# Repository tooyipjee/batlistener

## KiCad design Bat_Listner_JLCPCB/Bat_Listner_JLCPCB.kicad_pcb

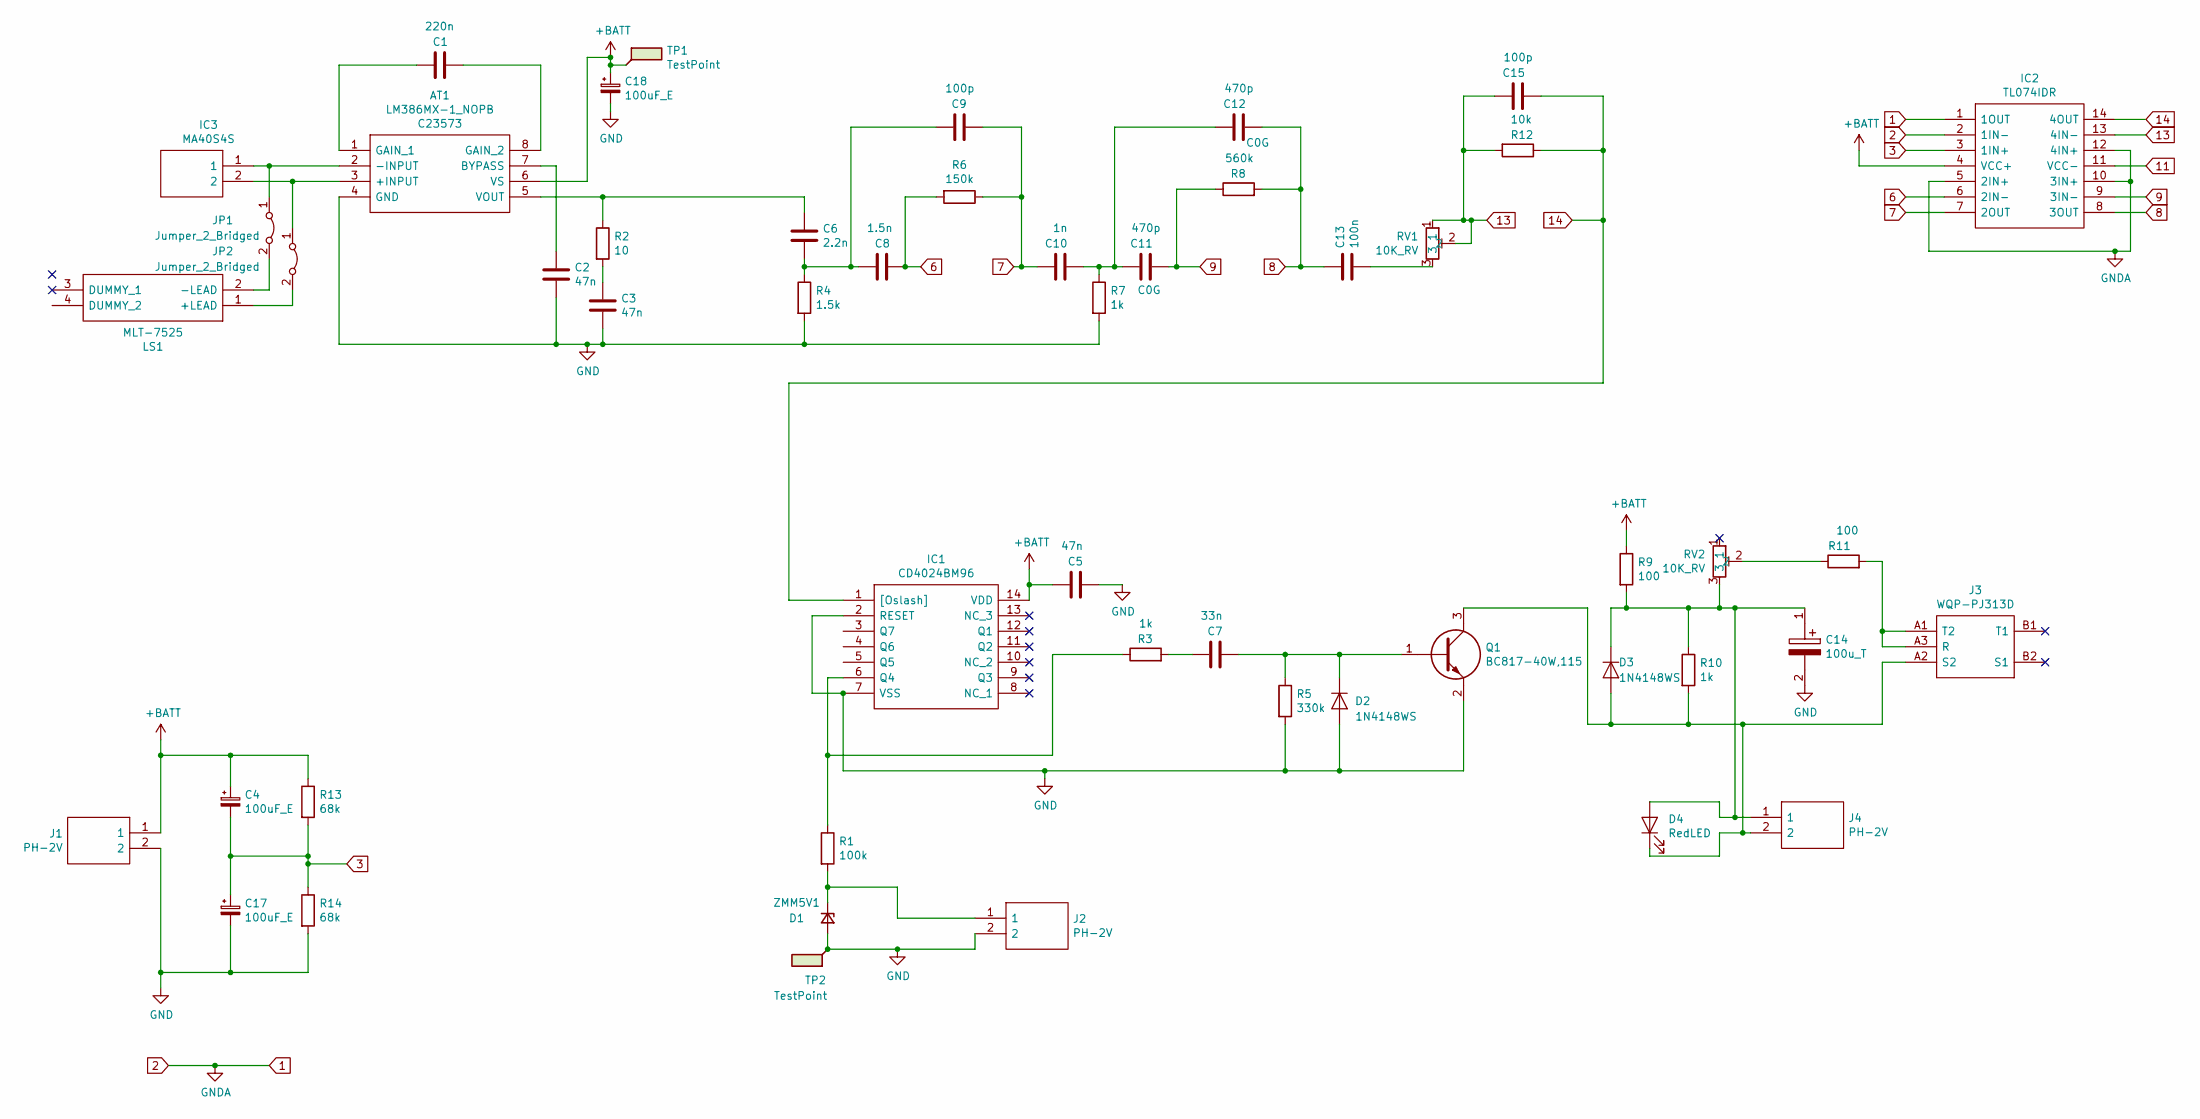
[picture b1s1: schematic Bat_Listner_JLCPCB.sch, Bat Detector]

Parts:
AT1: LM386MX-1_NOPB; SOIC127P600X175-8N; Manufacturer_Part_Number LM386MX-1/NOPB; Mouser Part Number 926-LM386MX-1/NOPB
C1: 220n; C_0402_1005Metric; LCSC C16772
C2, C3, C5: 47n; C_0402_1005Metric; LCSC C26403
C4, C17, C18: 100uF_E; CP_Elec_6.3x7.7; Rating 25V; LCSC C127971
C6: 2.2n; C_0402_1005Metric; LCSC C1531
C7: 33n; C_0402_1005Metric; LCSC C1585
C8: 1.5n; C_0402_1005Metric; LCSC C23967
C9, C15: 100p; C_0402_1005Metric; LCSC C1546
C10: 1n; C_0402_1005Metric; LCSC C1523
C11, C12: 470p; C_0603_1608Metric; Rating 25V; LCSC C1620
C13: 100n; C_0402_1005Metric; LCSC C307331
C14: 100u_T; CAPPM3528X210N; Mouser Part Number 581-TAJB107K006R
D1: ZMM5V1; D_MiniMELF; LCSC C8061
D2, D3: 1N4148WS; D_SOD-323F; LCSC C2128
D4: RedLED; D_0805_2012Metric; LCSC C84256
IC1: CD4024BM96; SOIC127P600X175-14N; Mouser Part Number 595-CD4024BM96
IC2: TL074IDR; SOIC127P600X175-14N; Manufacturer_Part_Number TL074IDR; Mouser Part Number 595-TL074IDR
IC3: MA40S4S; Mouser Part Number 81-MA40S4S
J1, J2, J4: PH-2V; SHDR2W52P0X200_1X2_600X460X630P; Manufacturer_Part_Number PH-2AK; Mouser Part Number 763-A2001WR2P
J3: WQP-PJ313D; C18167; Manufacturer_Part_Number C18167; LCSC C18167
JP1, JP2: Jumper_2_Bridged; SolderJumper-2_P1.3mm_Bridged_Pad1.0x1.5mm
LS1: MLT-7525; MLT7525; Manufacturer_Part_Number MLT-7525; LCSC C95299
Q1: BC817-40W,115; SOT65P210X110-3N; Manufacturer_Part_Number BC817-40W,115; Mouser Part Number 771-BC817-40W-T/R
R1: 100k; R_0402_1005Metric; LCSC C25741
R2: 10; R_0603_1608Metric; LCSC C25077
R3, R7, R10: 1k; R_0402_1005Metric; LCSC C11702
R4: 1.5k; R_0402_1005Metric; LCSC C25867
R5: 330k; R_0402_1005Metric; LCSC C25778
R6: 150k; R_0402_1005Metric; LCSC C25755
R8: 560k; R_0603_1608Metric; LCSC C23203
R9, R11: 100; R_0402_1005Metric; LCSC C25076
R12: 10k; R_0402_1005Metric; LCSC C25744
R13, R14: 68k; R_0402_1005Metric; LCSC C36871
RV1, RV2: 10K_RV; 3314J-1; Manufacturer_Part_Number 3314J-1-103E; Mouser Part Number 652-3314J-1-103E
TP1, TP2: TestPoint; TestPoint_Keystone_5000-5004_Miniature

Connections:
1: IC2.1 (1OUT), IC2.2 (1IN-), IC2.5 (2IN+), IC2.10 (3IN+), IC2.12 (4IN+)
3: C4.2, C17.1, IC2.3 (1IN+), R13.2, R14.1
6: C8.1, IC2.6 (2IN-), R6.2
7: C9.2, C10.1, IC2.7 (2OUT), R6.1
8: C12.2, C13.1, IC2.8 (3OUT), R8.2
9: C11.2, IC2.9 (3IN-), R8.1
13: C15.1, IC2.13 (4IN-), R12.2, RV1.1, RV1.2
14: C15.2, IC1.1 ([Oslash]), IC2.14 (4OUT), R12.1
+BATT: AT1.6 (VS), C4.1, C5.1, C18.1, IC1.14 (VDD), IC2.4 (VCC+), J1.1, R9.1, R13.1, TP1.1
GND: AT1.4 (GND), C2.2, C3.2, C5.2, C14.2, C17.2, C18.2, D1.2 (A), D2.2 (A), IC1.2 (RESET), IC1.7 (VSS), J1.2, J2.2, Q1.2, R4.2, R5.2, R7.2, R14.2, TP2.1
unnamed: AT1.1 (GAIN_1), C1.2
unnamed: AT1.2 (-INPUT), IC3.1, JP1.1 (A)
unnamed: AT1.3 (+INPUT), IC3.2, JP2.1 (A)
unnamed: AT1.5 (VOUT), C6.1, R2.1
unnamed: AT1.7 (BYPASS), C2.1
unnamed: AT1.8 (GAIN_2), C1.1
unnamed: C3.1, R2.2
unnamed: C6.2, C8.2, C9.1, R4.1
unnamed: C7.1, R3.2
unnamed: C7.2, D2.1 (K), Q1.1, R5.1
unnamed: C10.2, C11.1, C12.1, R7.1
unnamed: C13.2, RV1.3
unnamed: C14.1, D3.1 (K), D4.2 (A), J4.1, R9.2, R10.1, RV2.3
unnamed: D1.1 (K), J2.1, R1.2
unnamed: D3.2 (A), D4.1 (K), J3.A2 (S2), J4.2, Q1.3, R10.2
unnamed: IC1.6 (Q4), R1.1, R3.1
unnamed: J3.A1 (T2), J3.A3 (R), R11.2
unnamed: JP1.2 (B), LS1.2 (-LEAD)
unnamed: JP2.2 (B), LS1.1 (+LEAD)
unnamed: R11.1, RV2.2

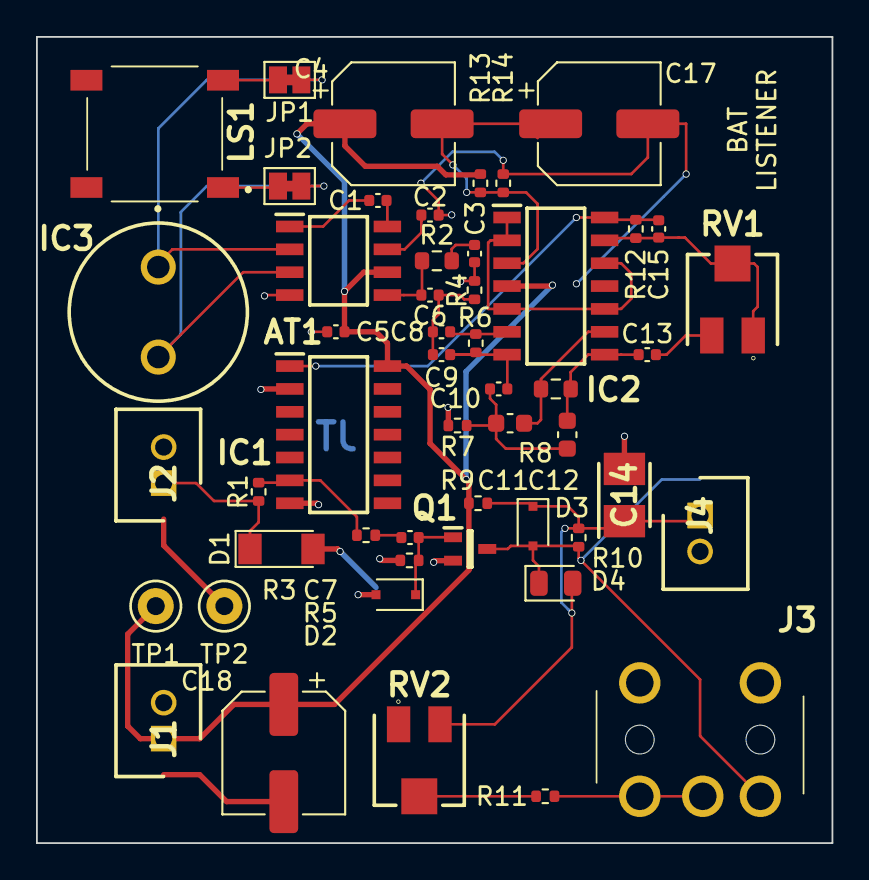
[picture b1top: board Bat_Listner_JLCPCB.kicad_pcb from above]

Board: 2 copper layers, 44.2 x 44.8 mm, 51 parts (0 on the bottom side), 30 nets.

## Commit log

2020-10-25 Created file for bat detector
2020-11-09 Preliminary part placement
2020-12-27 Finished schematic
2021-01-01 prelim layout with TPs
2021-01-05 finished layout
2021-01-14 Finished PCB
2021-01-15 release
2021-01-15 completed wiring
2021-01-31 updated pcb to fix audio jack
2021-02-05 updated design
2021-02-07 update mfg
2021-05-26 finished
